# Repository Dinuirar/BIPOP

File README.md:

# bipop

Board for Interfacing Peripherals and On-board computer

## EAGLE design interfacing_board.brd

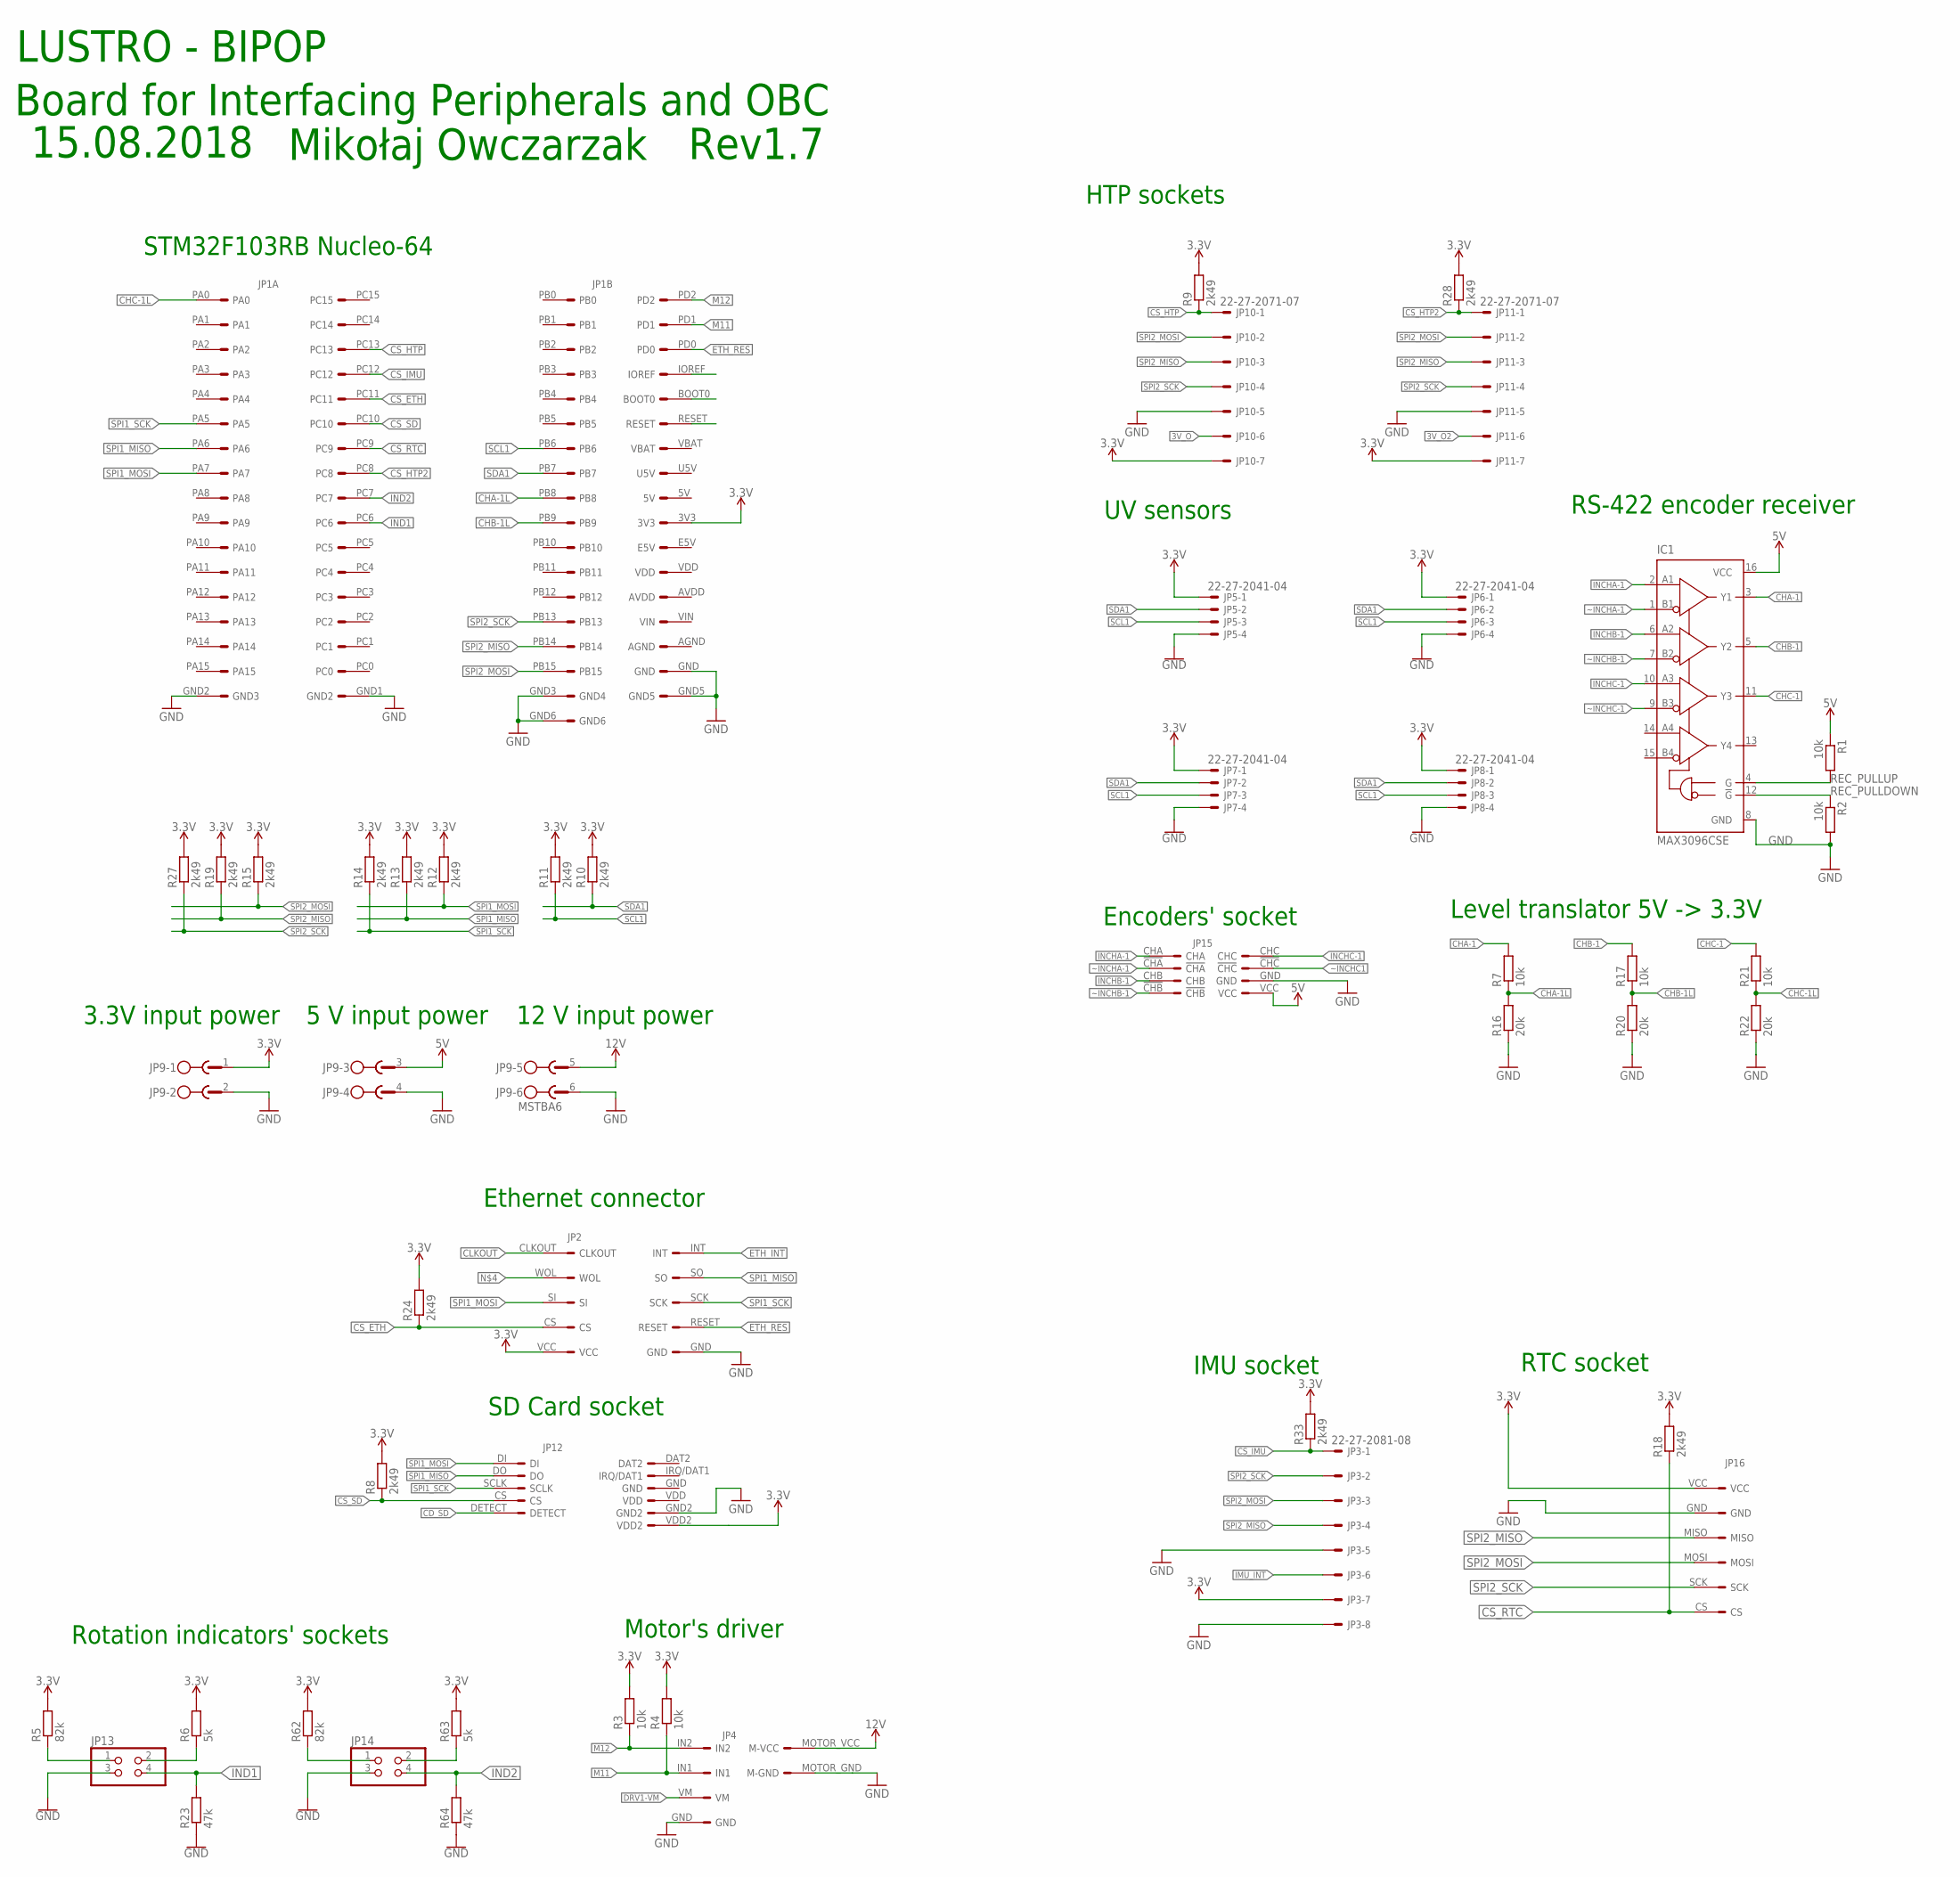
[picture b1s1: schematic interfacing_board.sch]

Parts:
IC1: MAX3096CSE; SO16
JP1A: JP1B; NUCLEO
JP2: ETHERNET
JP3: 22-27-2081-08; 6410-08
JP4: DRV8871; DRIVER
JP5, JP6, JP7, JP8: 22-27-2041-04; 6410-04
JP9: MSTBA6
JP10, JP11: 22-27-2071-07; 6410-07
JP12: SD_2597; SD
JP13, JP14: PINHD-2X2; 2X02
JP15: ENX10; SIL25
JP16: RTC_WAVESHARE; RTC
R1, R2, R3, R4, R7, R17, R21: 10k; M0805
R5, R62: 82k; M0805
R6, R63: 5k; M0805
R8, R9, R10, R11, R12, R13, R14, R15, R19, R24, R27, R28, R33: 2k49; M0805
R16, R20, R22: 20k; M0805
R18: 2k49; R0805
R23, R64: 47k; M0805

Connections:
3.3V: JP1A.3V3, JP2.VCC, JP3.7, JP5.1, JP6.1, JP7.1, JP8.1, JP9.1, JP10.7, JP11.7, JP12.VDD2, JP16.VCC, R3.2, R4.2, R5.2, R6.2, R8.2, R9.2, R10.2, R11.2, R12.2, R13.2, R14.2, R15.2, R18.2, R19.2, R24.2, R27.2, R28.2, R33.2, R62.2, R63.2
3V_O: JP10.6
3V_O2: JP11.6
5V: IC1.16 (VCC), JP9.3, JP15.VCC, R1.1
12V: JP4.MOTOR_VCC (M-VCC), JP9.5
CD_SD: JP12.DETECT
CHA-1: IC1.3 (Y1), R7.2
CHA-1L: JP1A.PB8, R7.1, R16.2
CHB-1: IC1.5 (Y2), R17.2
CHB-1L: JP1A.PB9, R17.1, R20.2
CHC-1: IC1.11 (Y3), R21.2
CHC-1L: JP1A.PA0, R21.1, R22.2
CLKOUT: JP2.CLKOUT
CS_ETH: JP1A.PC11, JP2.CS, R24.1
CS_HTP: JP1A.PC13, JP10.1, R9.1
CS_HTP2: JP1A.PC8, JP11.1, R28.1
CS_IMU: JP1A.PC12, JP3.1, R33.1
CS_RTC: JP1A.PC9, JP16.CS, R18.1
CS_SD: JP1A.PC10, JP12.CS, R8.1
DRV1-VM: JP4.VM
ETH_INT: JP2.INT
ETH_RES: JP1A.PD0, JP2.RESET
GND: IC1.8 (GND), JP1A.GND, JP1A.GND1 (GND2), JP1A.GND2 (GND3), JP1A.GND3 (GND4), JP1A.GND5, JP1A.GND6, JP2.GND, JP3.5, JP3.8, JP4.GND, JP4.MOTOR_GND (M-GND), JP5.4, JP6.4, JP7.4, JP8.4, JP9.2, JP9.4, JP9.6, JP10.5, JP11.5, JP12.GND2, JP13.3, JP14.3, JP15.GND, JP16.GND, R2.2, R16.1, R20.1, R22.1, R23.1, R64.1
IMU_INT: JP3.6
INCHA-1: IC1.2 (A1), JP15.CHA
INCHB-1: IC1.6 (A2), JP15.CHB
INCHC-1: IC1.10 (A3), JP15.CHC
IND1: JP1A.PC6, JP13.4, R23.2
IND2: JP1A.PC7, JP14.4, R64.2
M11: JP1A.PD1, JP4.IN1, R4.1
M12: JP1A.PD2, JP4.IN2, R3.1
unnamed: JP13.2, R6.1
unnamed: JP13.1, R5.1
unnamed: JP14.2, R63.1
unnamed: JP14.1, R62.1
REC_PULLDOWN: IC1.12 (!G), R2.1
REC_PULLUP: IC1.4 (G), R1.2
SCL1: JP1A.PB6, JP5.3, JP6.3, JP7.3, JP8.3, R11.1
SDA1: JP1A.PB7, JP5.2, JP6.2, JP7.2, JP8.2, R10.1
SPI1_MISO: JP1A.PA6, JP2.SO, JP12.DO, R13.1
SPI1_MOSI: JP1A.PA7, JP2.SI, JP12.DI, R12.1
SPI1_SCK: JP1A.PA5, JP2.SCK, JP12.SCLK, R14.1
SPI2_MISO: JP1A.PB14, JP3.4, JP10.3, JP11.3, JP16.MISO, R19.1
SPI2_MOSI: JP1A.PB15, JP3.3, JP10.2, JP11.2, JP16.MOSI, R15.1
SPI2_SCK: JP1A.PB13, JP3.2, JP10.4, JP11.4, JP16.SCK, R27.1
~INCHA-1: IC1.1 (B1), JP15.!CHA
~INCHB-1: IC1.7 (B2), JP15.!CHB
~INCHC1: JP15.!CHC
~INCHC-1: IC1.9 (B3)

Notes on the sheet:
SD Card socket
3.3V input power
STM32F103RB Nucleo-64
Ethernet connector
UV sensors
IMU socket
HTP sockets
12 V input power
Motor's driver
Board for Interfacing Peripherals and OBC
Rev1.7
LUSTRO - BIPOP
15.08.2018
Mikołaj Owczarzak
Rotation indicators' sockets
RTC socket
5 V input power
Encoders' socket
RS-422 encoder receiver
Level translator 5V -> 3.3V

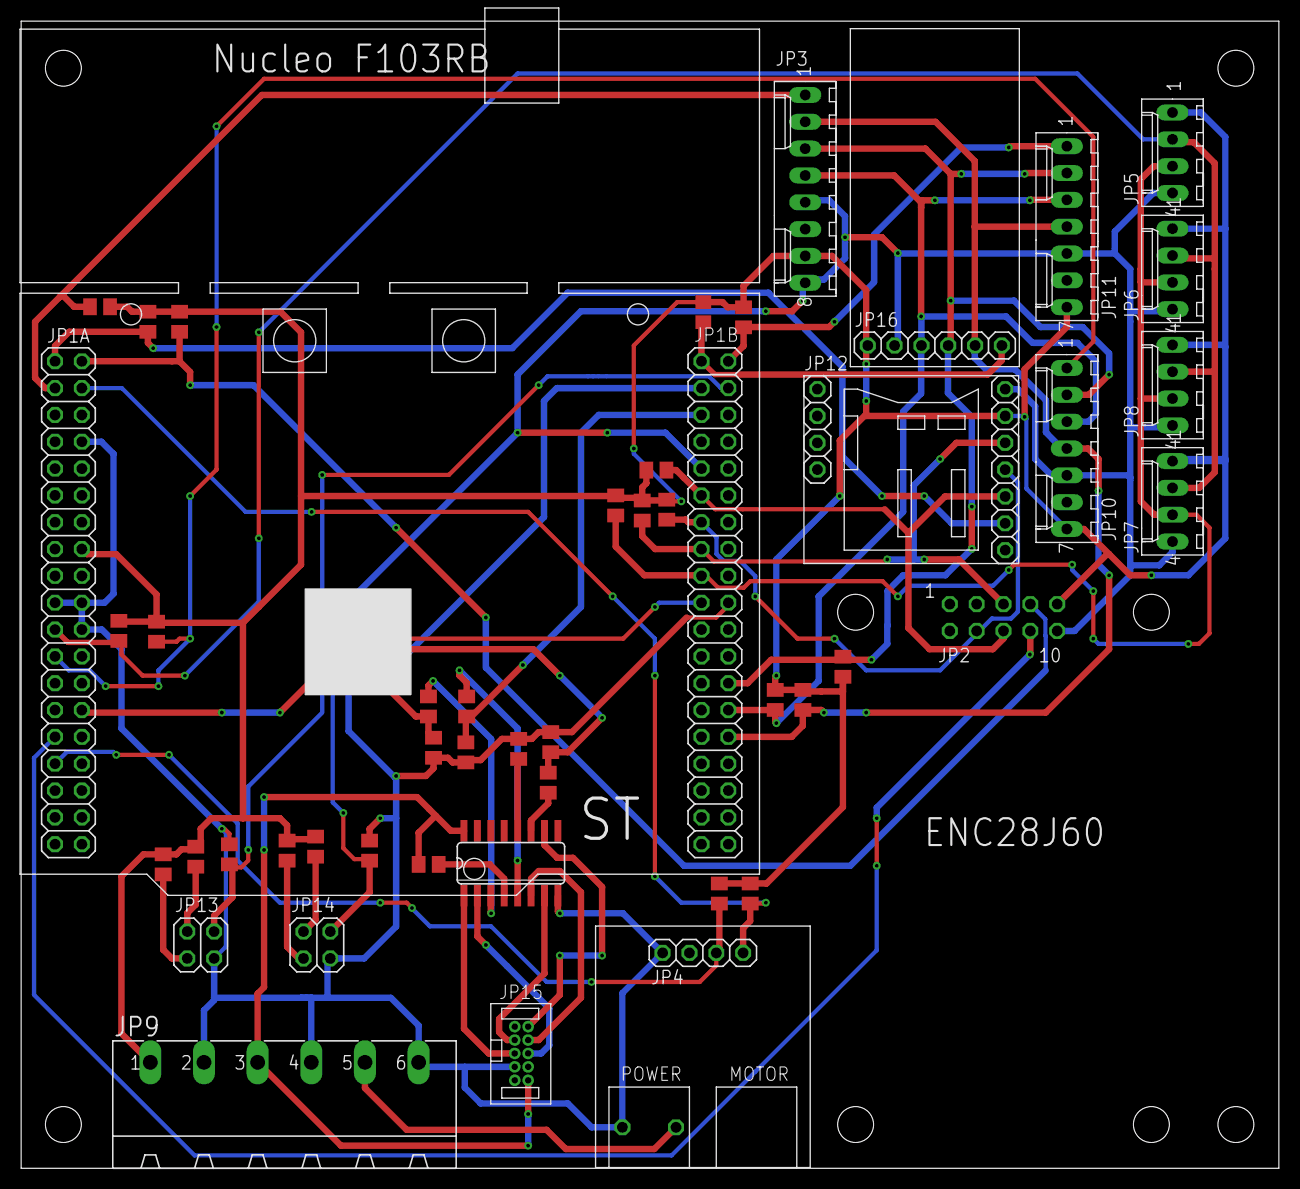
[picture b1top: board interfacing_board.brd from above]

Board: 2 copper layers, 119.1 x 108.6 mm, 47 parts (1 on the bottom side), 40 nets.

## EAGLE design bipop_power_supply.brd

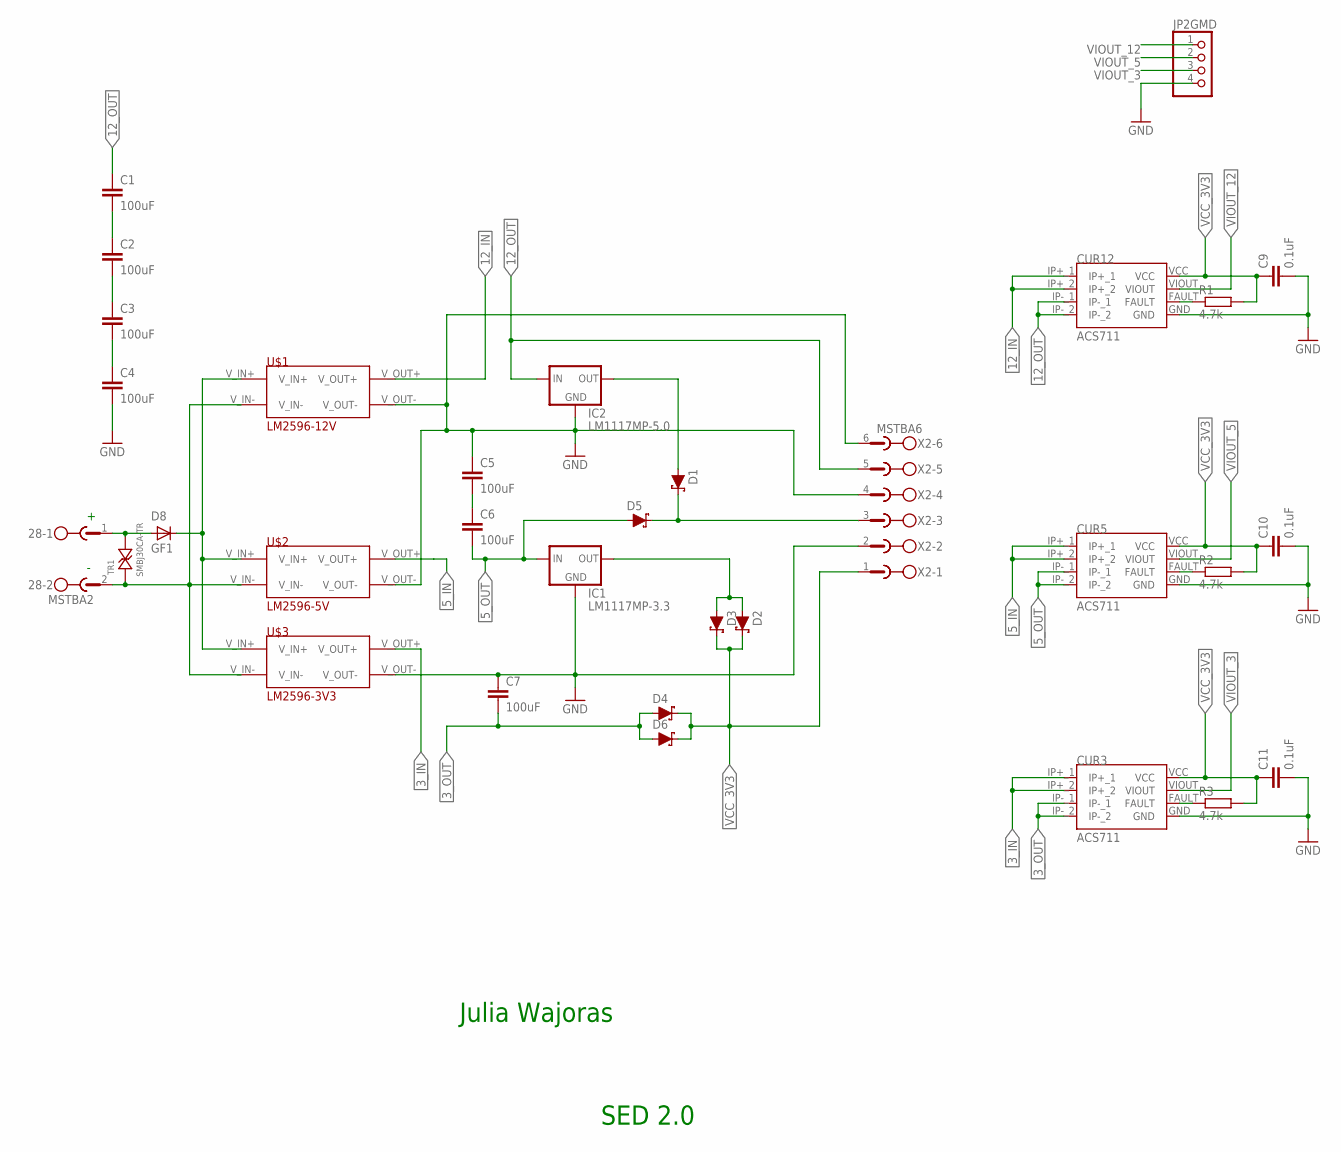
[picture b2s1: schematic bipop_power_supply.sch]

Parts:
28: MSTBA2
C1, C2, C3, C4, C5, C6, C7: 100uF; C0805
C9, C10, C11: 0.1uF; C0805
CUR3, CUR5, CUR12: ACS711
D1, D2, D3, D4, D5, D6: DIODE-SCHOTTKY-BAT20J; SOD-323
D8: GF1; SMA-DO214AC
IC1: LM1117MP-3.3; SOT223
IC2: LM1117MP-5.0; SOT223
JP2GMD: PINHD-1X4; 1X04
R1, R2, R3: 4.7k; R0805
TR1: SMBJ30CA-TR; DO214AC_BIDIR
U$1: LM2596-12V; DC-DC_CONVERTER
U$2: LM2596-5V; DC-DC_CONVERTER
U$3: LM2596-3V3; DC-DC_CONVERTER
X2: MSTBA6

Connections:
3_IN: CUR3.IP+_1, CUR3.IP+_2, U$3.V_OUT+
3_OUT: C7.2, CUR3.IP-_1, CUR3.IP-_2, D4.A, D6.A
5_IN: CUR5.IP+_1, CUR5.IP+_2, U$2.V_OUT+
5_OUT: C6.2, CUR5.IP-_1, CUR5.IP-_2, D5.A, IC1.3 (IN)
12_IN: CUR12.IP+_1, CUR12.IP+_2, U$1.V_OUT+
12_OUT: C1.1, CUR12.IP-_1, CUR12.IP-_2, IC2.3 (IN), X2.5
GND: C4.2, C5.1, C7.1, C9.2, C10.2, C11.2, CUR3.GND, CUR5.GND, CUR12.GND, IC1.1 (GND), IC2.1 (GND), JP2GMD.4, U$1.V_OUT-, U$2.V_OUT-, U$3.V_OUT-, X2.2, X2.4, X2.6
MM: D8.K (C), U$1.V_IN+, U$2.V_IN+, U$3.V_IN+
unnamed: CUR3.FAULT, R3.1
unnamed: C2.2, C3.1
unnamed: D1.A, IC2.2 (OUT)
unnamed: CUR5.FAULT, R2.1
unnamed: D2.A, D3.A, IC1.2 (OUT)
unnamed: C3.2, C4.1
unnamed: CUR12.FAULT, R1.1
unnamed: C5.2, C6.1
unnamed: C1.2, C2.1
unnamed: 28.2, TR1.P$1, U$1.V_IN-, U$2.V_IN-, U$3.V_IN-
unnamed: 28.1, D8.A, TR1.P$2
unnamed: D1.C, D5.C, X2.3
VCC_3V3: C9.1, C10.1, C11.1, CUR3.VCC, CUR5.VCC, CUR12.VCC, D2.C, D3.C, D4.C, D6.C, R1.2, R2.2, R3.2, X2.1
VIOUT_3: CUR3.VIOUT, JP2GMD.3
VIOUT_5: CUR5.VIOUT, JP2GMD.2
VIOUT_12: CUR12.VIOUT, JP2GMD.1

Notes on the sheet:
Julia Wajoras
SED 2.0

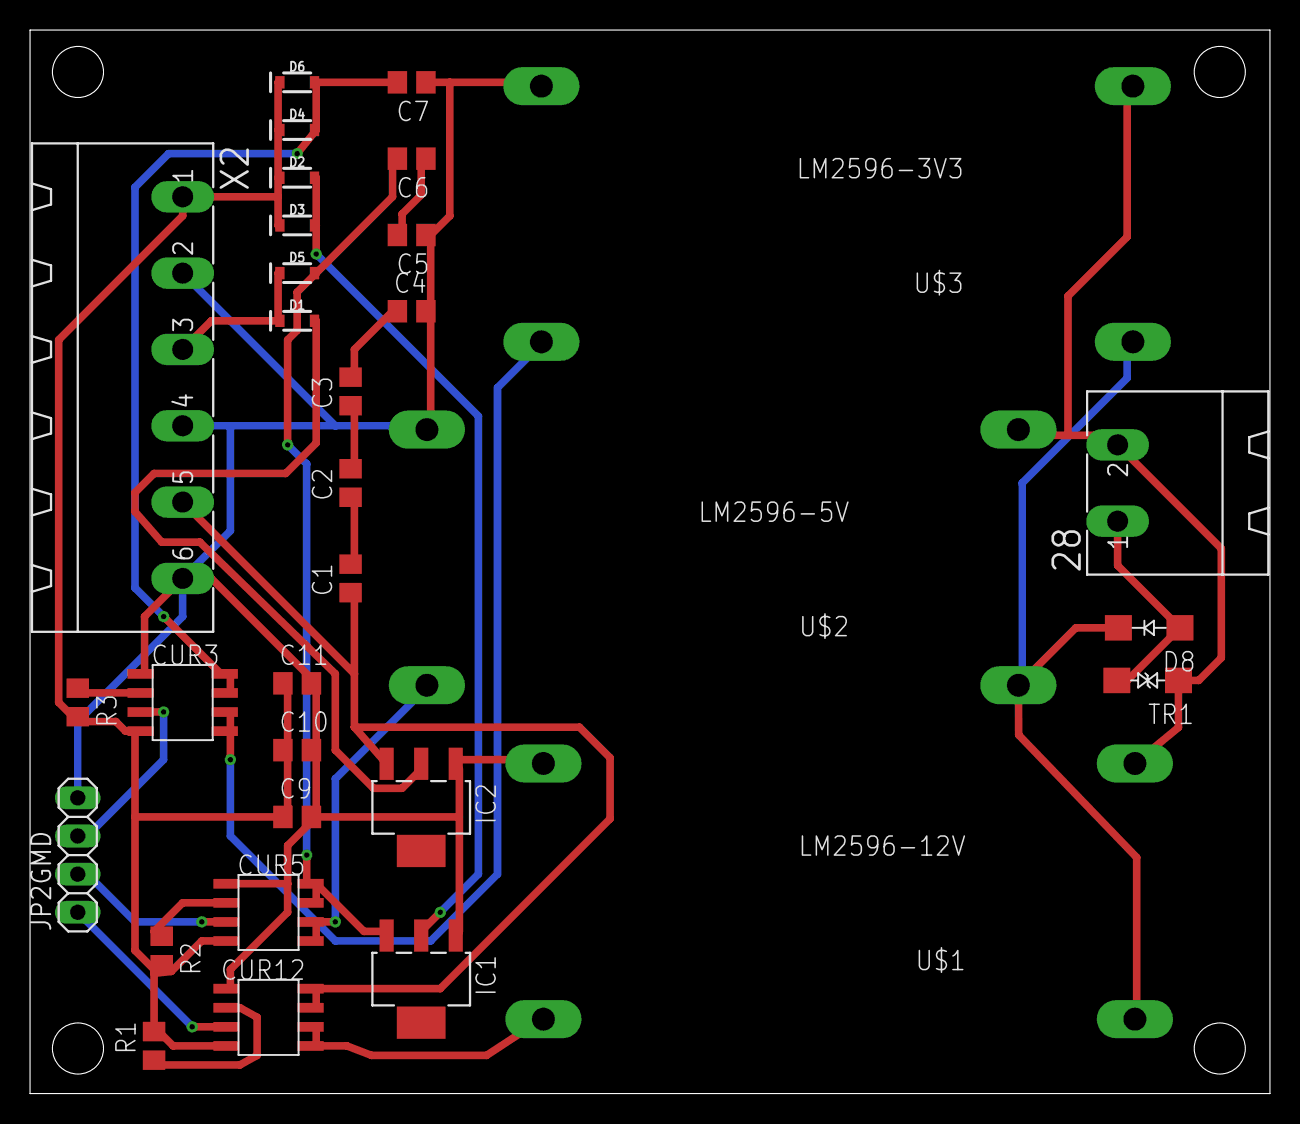
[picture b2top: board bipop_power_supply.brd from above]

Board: 2 copper layers, 82.5 x 70.8 mm, 33 parts (0 on the bottom side), 24 nets.

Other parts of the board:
U$4: A5P-LOC

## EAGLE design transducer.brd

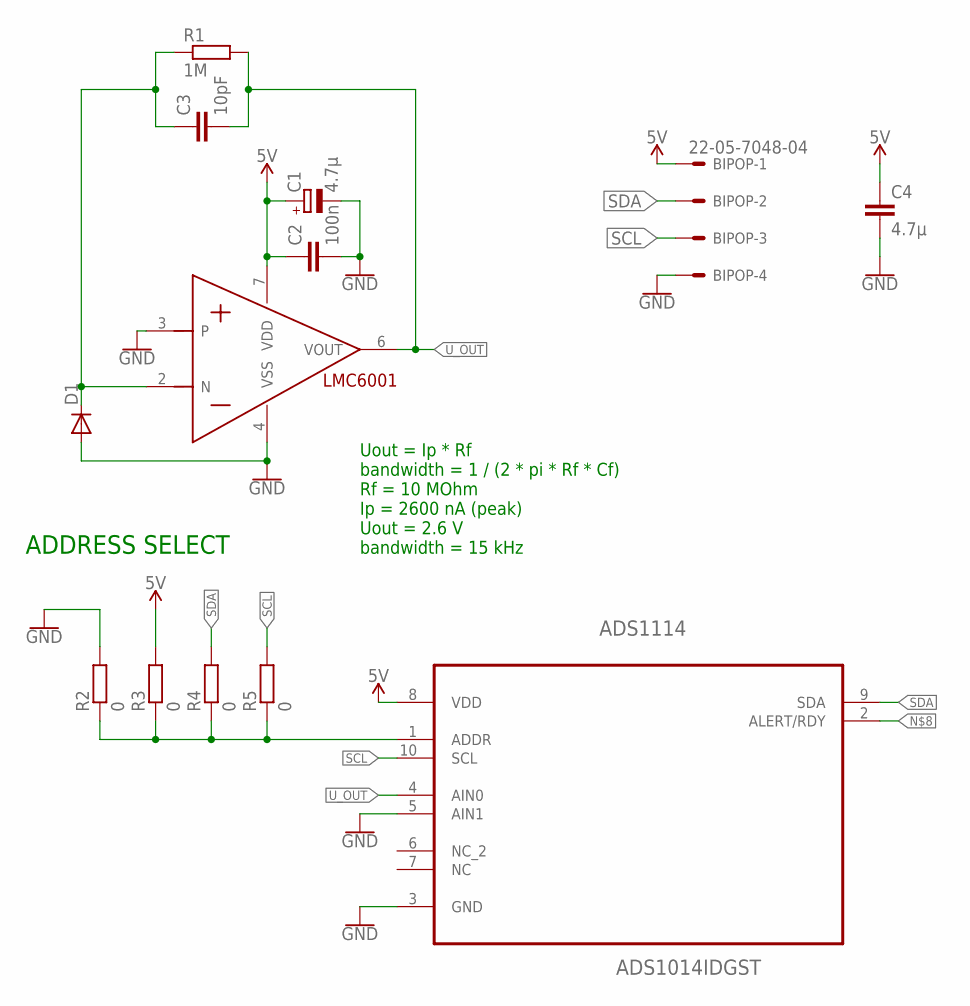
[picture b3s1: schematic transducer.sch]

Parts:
ADS1114: ADS1014IDGST; SOP50P490X110-10N
BIPOP: 22-05-7048-04; 7395-04
C1: 4.7µ; A/3216-18R
C2: 100n; C0805
C3: 10pF; C0603
C4: 4.7µ; C0805
D1: DIODE-TO18D; TO18D
LMC6001: LMC6001; DIL08
R1: 1M; R0805
R2, R3, R4, R5: 0; R0805

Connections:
5V: ADS1114.8 (VDD), BIPOP.1, C1.+, C2.1, C4.1, LMC6001.7 (VDD), R3.2
ADR: ADS1114.1 (ADDR), R2.1, R3.1, R4.1, R5.1
CATH: C3.1, D1.C, LMC6001.2 (N), R1.1
GND: ADS1114.3 (GND), ADS1114.5 (AIN1), BIPOP.4, C1.-, C2.2, C4.2, D1.A, LMC6001.3, LMC6001.4 (VSS), R2.2
SCL: ADS1114.10 (SCL), BIPOP.3, R5.2
SDA: ADS1114.9 (SDA), BIPOP.2, R4.2
U_OUT: ADS1114.4 (AIN0), C3.2, LMC6001.6 (VOUT), R1.2

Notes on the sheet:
Uout = Ip * Rf bandwidth = 1 / (2 * pi * Rf * Cf) Rf = 10 MOhm Ip = 2600 nA (peak) Uout = 2.6 V bandwidth = 15 kHz
ADDRESS SELECT

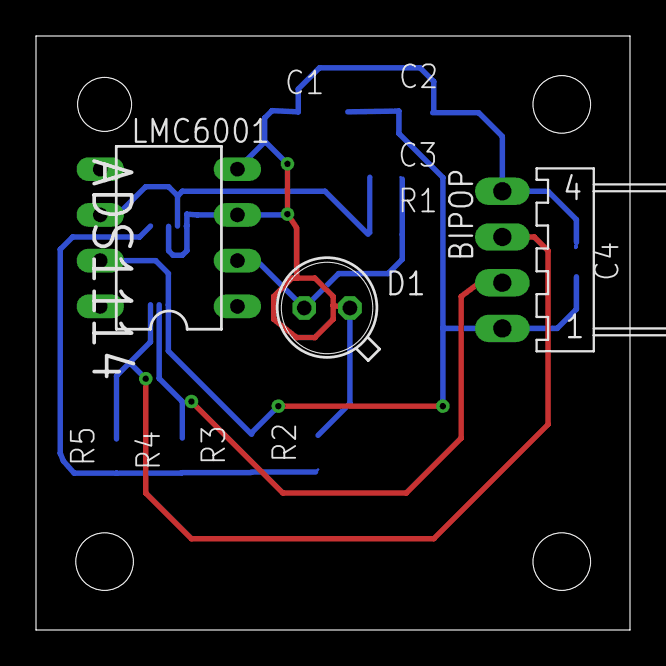
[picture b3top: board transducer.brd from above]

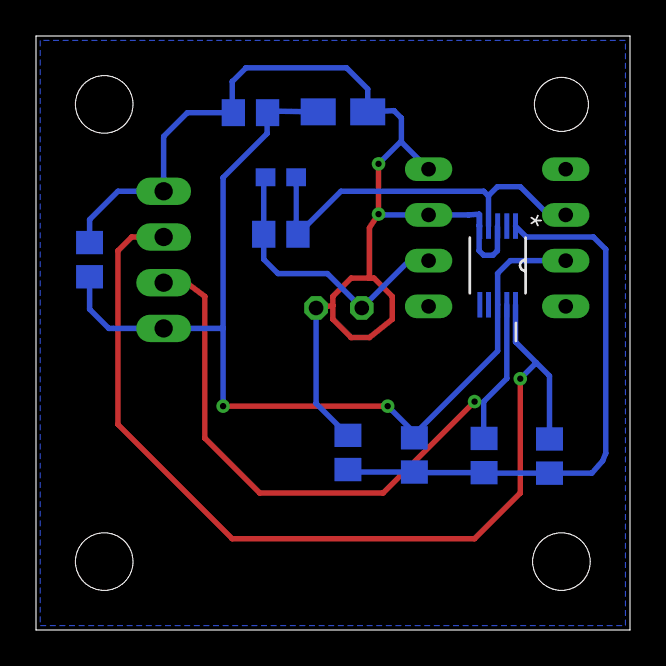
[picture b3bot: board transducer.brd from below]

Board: 2 copper layers, 33.0 x 33.0 mm, 13 parts (10 on the bottom side), 7 nets.

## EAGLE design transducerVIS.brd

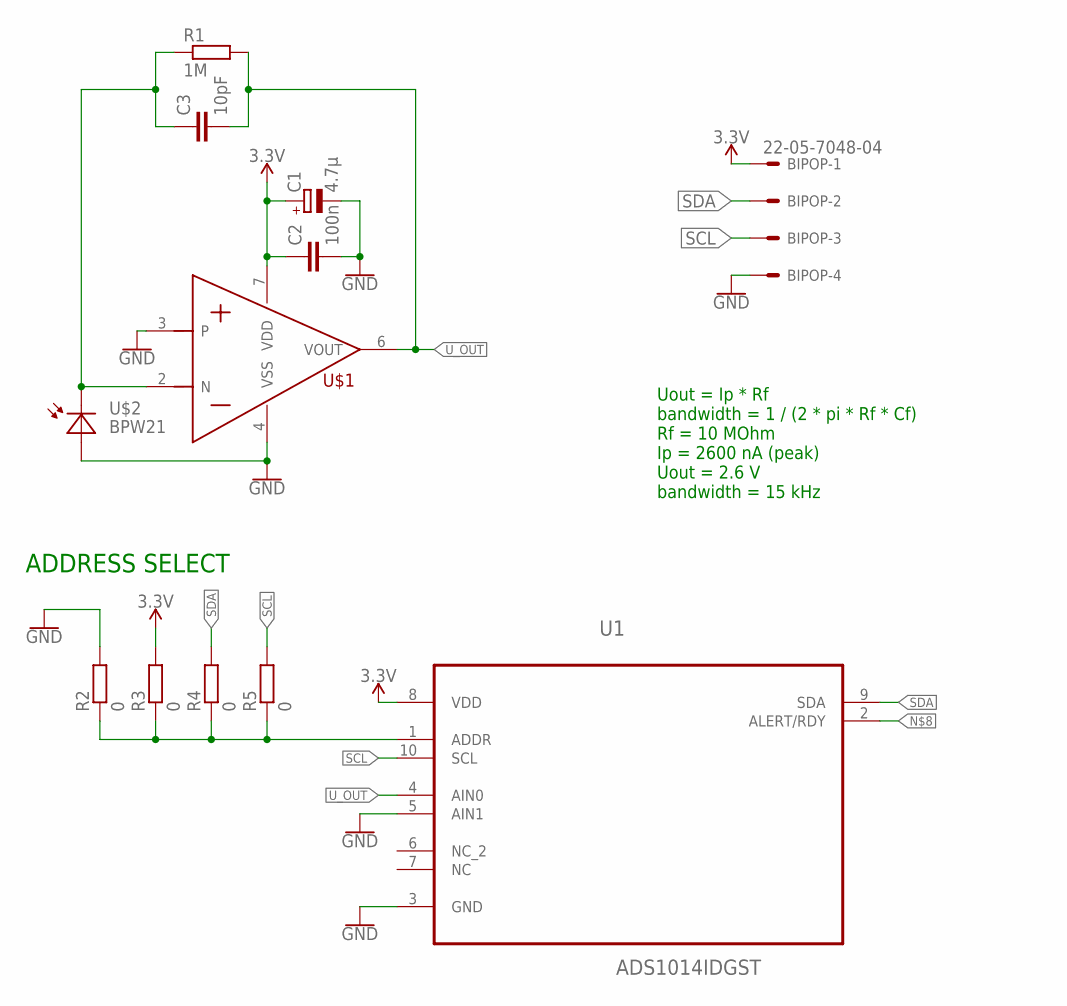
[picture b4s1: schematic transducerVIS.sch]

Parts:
BIPOP: 22-05-7048-04; 7395-04
C1: 4.7µ; A/3216-18R
C2: 100n; C0805
C3: 10pF; C0603
R1: 1M; R0805
R2, R3, R4, R5: 0; R0805
U1: ADS1014IDGST; SOP50P490X110-10N
U$1: LMC6001; DIL08
U$2: BPW21; TO52

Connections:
3.3V: BIPOP.1, C1.+, C2.1, R3.2, U1.8 (VDD), U$1.7 (VDD)
GND: BIPOP.4, C1.-, C2.2, R2.2, U1.3 (GND), U1.5 (AIN1), U$1.3, U$1.4 (VSS), U$2.1 (A)
unnamed: R2.1, R3.1, R4.1, R5.1, U1.1 (ADDR)
unnamed: C3.1, R1.1, U$1.2 (N), U$2.2 (C)
SCL: BIPOP.3, R5.2, U1.10 (SCL)
SDA: BIPOP.2, R4.2, U1.9 (SDA)
U_OUT: C3.2, R1.2, U1.4 (AIN0), U$1.6 (VOUT)

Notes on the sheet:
Uout = Ip * Rf bandwidth = 1 / (2 * pi * Rf * Cf) Rf = 10 MOhm Ip = 2600 nA (peak) Uout = 2.6 V bandwidth = 15 kHz
ADDRESS SELECT

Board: 2 copper layers, 12 parts (0 on the bottom side), 7 nets, no tracks yet.

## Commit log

2018-05-14 SED2.0 version
2018-05-14 Rev1.9. Small board, autorouted. Too thin routes. For SED2.0
2018-05-20 transducer boards for photodiodes added (todo: routing)
2018-05-20 deleted photodiode sockets and their amplifiers on interfacing board schematic and PCB
2018-05-22 updated pullups
2018-05-23 added bipop_power_supply .sch .brd with capacitors, transil and diode; .sch to CHECK; .brd TODO
2018-05-25 .sch z diodami i kondensatorami, .brd TODO
2018-05-25 plytka z kondensatorami i diodami +pdfy
2018-05-25 added diodes, capacitors
2018-05-26 BIPOP updated. Grid errors corrected, pull-ups for CS pins added.
2018-05-26 Autorouter on BIPOP board.
2018-05-26 Transducer board routed.
2018-05-26 Changed connector in bipop_power_supply board, modified routing and board's dimensions.
2018-05-27 Fixed polarisation in power_supply board.
2018-05-27 Libraries with modified or custom elements added.
2018-05-27 interfaces_block.xml
2018-05-27 Rename interfejsy (2) (3) (2).xml to interfaces_block.xml
2018-06-21 Preparing for the menufacturing
2018-06-23 Circuit converted to single-periscope operation mode. Duplicate components removed.
2018-06-24 Schematics reorganised to be more readable.
2018-06-24 Block diagrams (power supply and interfaces) added. bipop_pinout.ods file moved.
2018-07-26 UV transducer board redesigned according to SGlux tips
2018-07-28 Transducer power supply and routing modified.
2018-07-28 Nucleo and ethernet module library components added. Implemented in schematics and PCB. Redesign of the PCB, errors removal.
2018-07-29 transducer redesigned - alternative
2018-07-29 SGlux version of transducer, new lib elements, transVIS deleted
2018-07-29 BIPOP board redesigned, new versions of transducers added.
2018-08-02 added current sensors to power supply, NO ADC yet
2018-08-07 pin interface for current sensors added
2018-08-08 minor changes in PoSup PCB design
2018-08-08 poprawione, dodane pullupy do czujnikow pradu
2018-08-09 PS poprawione, dodane pullupy
2018-08-10 Minor PoSup layout changes
2018-08-14 changed diodes' packages
2018-08-15 small board adjustments, ready to gerber
2018-08-15 gerber files added
2018-08-15 Further footprint updates, BIPOP v. 1.8 ready to order.
2018-12-23 poprawione routowanie
2018-12-25 refit

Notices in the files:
parts and their libraries:
sparkfun-discrete-semi: Licensing: Creative Commons ShareAlike 4.0 International - https://creativecommons.org/licenses/by-sa/4.0
